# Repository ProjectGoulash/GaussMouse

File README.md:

# GaussMouse
The Project Goulash version of a DIY spacemouse

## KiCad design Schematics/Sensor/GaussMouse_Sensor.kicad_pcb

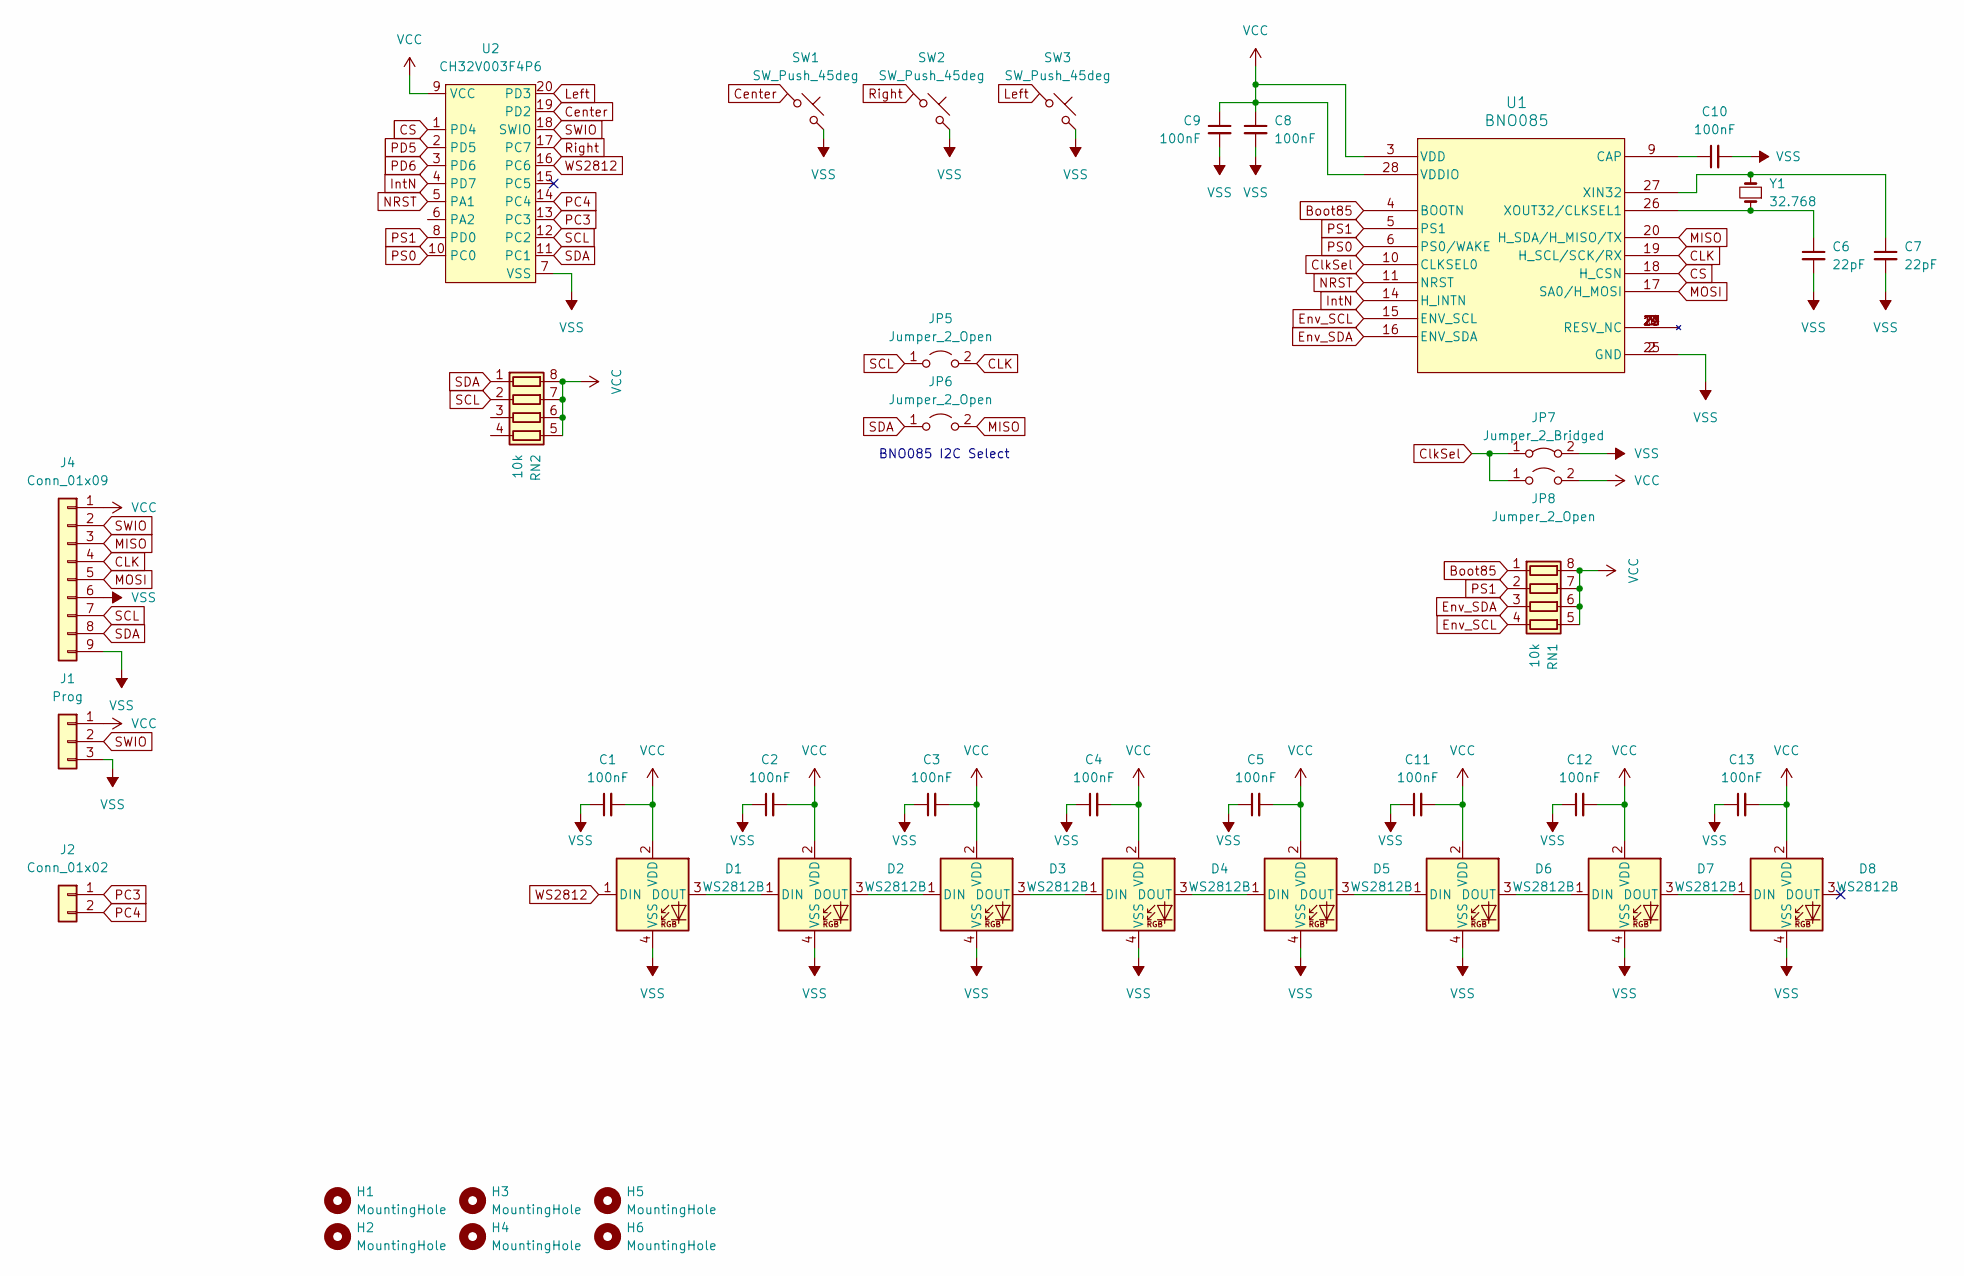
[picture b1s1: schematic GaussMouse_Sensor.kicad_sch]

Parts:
C1, C2, C3, C4, C5, C8, C9, C10, C11, C12, C13: 100nF; C_0805_2012Metric
C6, C7: 22pF; C_0805_2012Metric
D1, D2, D3, D4, D5, D6, D7, D8: WS2812B; SK6812SIDE-A-RVS
H1, H2, H3, H4, H5, H6: MountingHole; MountingHole_2.2mm_M2
J1: Prog; PinHeader_1x03_P2.54mm_Vertical
J2: Conn_01x02; PinHeader_1x02_P2.54mm_Vertical
J4: Conn_01x09; CON_526100933_MOL
JP5, JP6, JP8: Jumper_2_Open; SolderJumper-2_P1.3mm_Open_TrianglePad1.0x1.5mm
JP7: Jumper_2_Bridged; SolderJumper-2_P1.3mm_Bridged_Pad1.0x1.5mm
RN1, RN2: 10k; R_Array_Convex_4x0603
SW1, SW2, SW3: SW_Push_45deg; SW_SPST_TL3342
U1: BNO085; LGA-28_5.2x3.8mm_P0.5mm
U2: CH32V003F4P6; TSSOP-20_4.4x6.5mm_P0.65mm
Y1: 32.768; Crystal_SMD_3215-2Pin_3.2x1.5mm

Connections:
Boot85: RN1.1 (R1.1), U1.4 (BOOTN)
CLK: J4.4, JP5.2 (B), U1.19 (H_SCL/SCK/RX)
CS: U1.18 (H_CSN), U2.1 (PD4)
Center: SW1.1, U2.19 (PD2)
ClkSel: JP7.1 (A), JP8.1 (A), U1.10 (CLKSEL0)
Env_SCL: RN1.4 (R4.1), U1.15 (ENV_SCL)
Env_SDA: RN1.3 (R3.1), U1.16 (ENV_SDA)
IntN: U1.14 (H_INTN), U2.4 (PD7)
Left: SW3.1, U2.20 (PD3)
MISO: J4.3, JP6.2 (B), U1.20 (H_SDA/H_MISO/TX)
MOSI: J4.5, U1.17 (SA0/H_MOSI)
NRST: U1.11 (NRST), U2.5 (PA1)
unnamed: D1.3 (DOUT), D2.1 (DIN)
unnamed: D2.3 (DOUT), D3.1 (DIN)
unnamed: D3.3 (DOUT), D4.1 (DIN)
unnamed: D4.3 (DOUT), D5.1 (DIN)
unnamed: D5.3 (DOUT), D6.1 (DIN)
unnamed: D6.3 (DOUT), D7.1 (DIN)
unnamed: D7.3 (DOUT), D8.1 (DIN)
unnamed: C10.1, U1.9 (CAP)
unnamed: C7.1, U1.27 (XIN32), Y1.2
unnamed: C6.1, U1.26 (XOUT32/CLKSEL1), Y1.1
PC3: J2.1, U2.13 (PC3)
PC4: J2.2, U2.14 (PC4)
PD5: U2.2 (PD5)
PD6: U2.3 (PD6)
PS0: U1.6 (PS0/WAKE), U2.10 (PC0)
PS1: RN1.2 (R2.1), U1.5 (PS1), U2.8 (PD0)
Right: SW2.1, U2.17 (PC7)
SCL: J4.7, JP5.1 (A), RN2.2 (R2.1), U2.12 (PC2)
SDA: J4.8, JP6.1 (A), RN2.1 (R1.1), U2.11 (PC1)
SWIO: J1.2, J4.2, U2.18 (SWIO)
VCC: C1.2, C2.2, C3.2, C4.2, C5.2, C8.1, C9.1, C11.2, C12.2, C13.2, D1.2 (VDD), D2.2 (VDD), D3.2 (VDD), D4.2 (VDD), D5.2 (VDD), D6.2 (VDD), D7.2 (VDD), D8.2 (VDD), J1.1, J4.1, JP8.2 (B), RN1.5 (R4.2), RN1.6 (R3.2), RN1.7 (R2.2), RN1.8 (R1.2), RN2.5 (R4.2), RN2.6 (R3.2), RN2.7 (R2.2), RN2.8 (R1.2), U1.3 (VDD), U1.28 (VDDIO), U2.9 (VCC)
VSS: C1.1, C2.1, C3.1, C4.1, C5.1, C6.2, C7.2, C8.2, C9.2, C10.2, C11.1, C12.1, C13.1, D1.4 (VSS), D2.4 (VSS), D3.4 (VSS), D4.4 (VSS), D5.4 (VSS), D6.4 (VSS), D7.4 (VSS), D8.4 (VSS), J1.3, J4.6, J4.9, JP7.2 (B), SW1.2, SW2.2, SW3.2, U1.2 (GND), U1.25 (GND), U2.7 (VSS)
WS2812: D1.1 (DIN), U2.16 (PC6)

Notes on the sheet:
BNO085 I2C Select

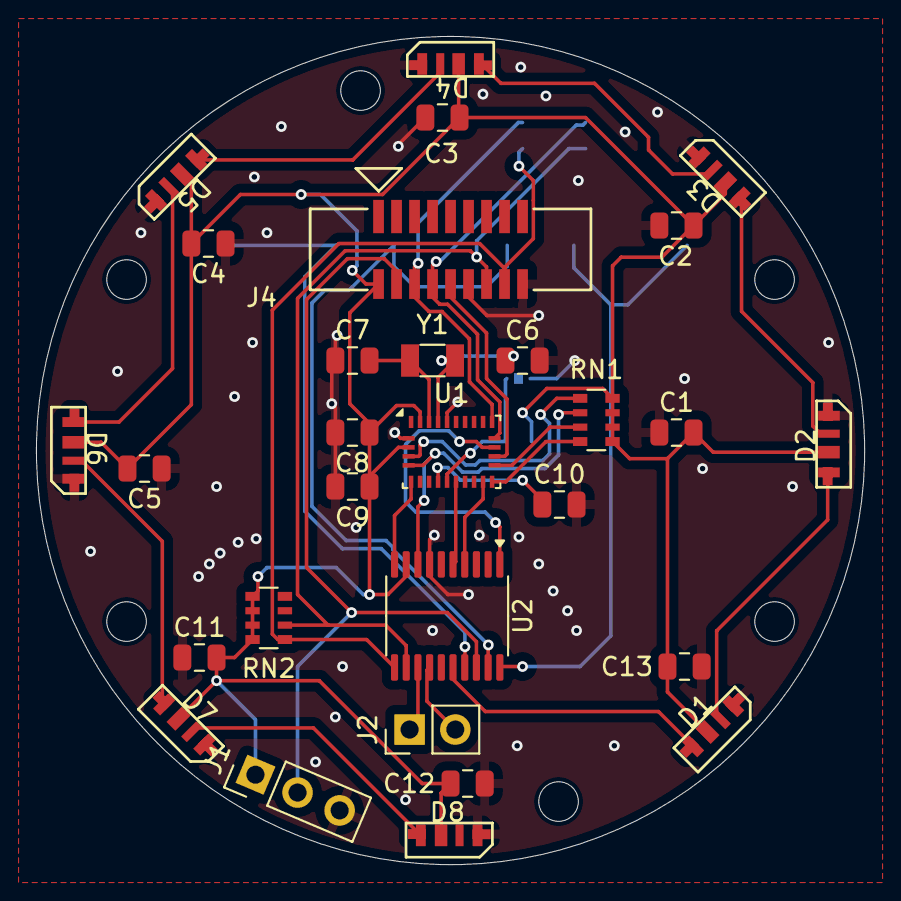
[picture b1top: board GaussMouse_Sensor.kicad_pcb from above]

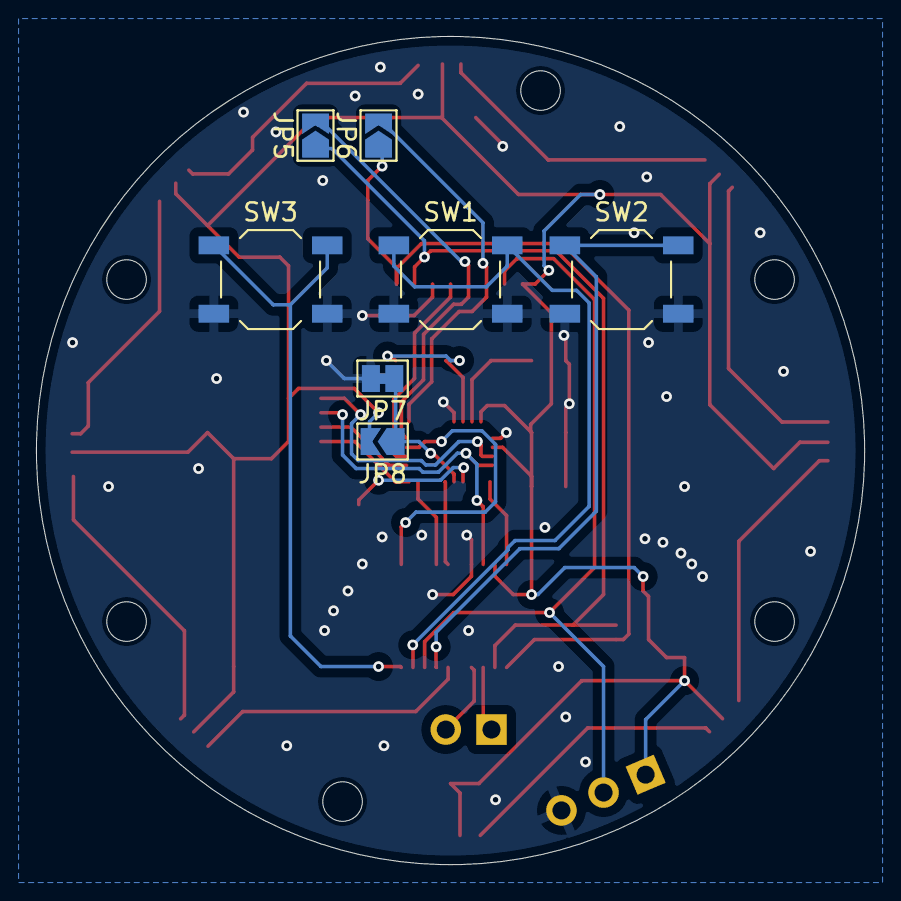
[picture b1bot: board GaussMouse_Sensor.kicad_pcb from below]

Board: 2 copper layers, 46.0 x 46.0 mm, 42 parts (7 on the bottom side), 33 nets.

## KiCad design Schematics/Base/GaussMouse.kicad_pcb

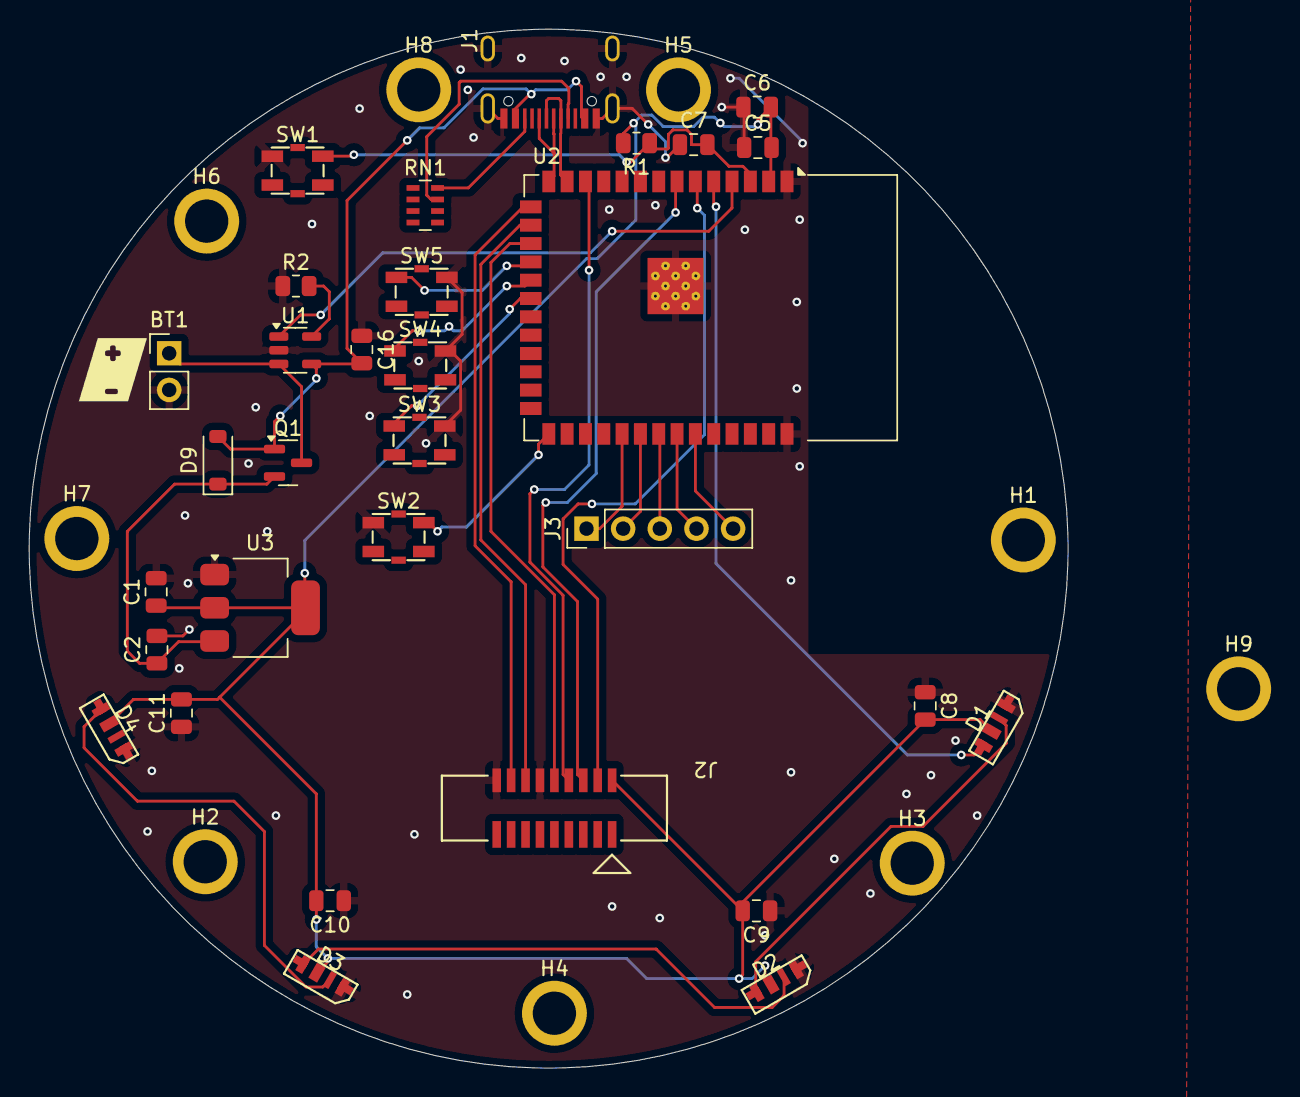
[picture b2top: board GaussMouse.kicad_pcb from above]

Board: 2 copper layers, 72.0 x 72.0 mm, 41 parts (0 on the bottom side), 31 nets.

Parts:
BT1: Battery_Cell; PinHeader_1x02_P2.54mm_Vertical
C1, C2: 10uF; C_0805_2012Metric
C5, C7, C8, C9, C10, C11: 100nF; C_0805_2012Metric
C6, C16: 22uF; C_0805_2012Metric
D1, D2, D3, D4: WS2812B; SK6812SIDE-A-RVS
D9: D_Schottky; D_SOD-123
H1, H2, H3, H4, H5, H6, H7, H8, H9: MountingHole; M2ThreadedStandoff
J1: USB_C_Receptacle; USB_C_Receptical-Jing
J2: Conn_01x09; CON_526100933_MOL
J3: Conn_01x05; PinHeader_1x05_P2.54mm_Vertical
Q1: AO3401A; SOT-23
R1, R2: R_Small; R_0805_2012Metric
RN1: 5.1k; R_Array_Concave_4x0603
SW1, SW2: SW_SPST; TS3315A
SW3, SW4, SW5: SW_Push_45deg; TS3315A
U1: LTC4054ES5; TSOT-23-5
U2: ESP32-S3-WROOM-1
U3: TLV1117-33; SOT-223-3_TabPin2
kibuzzard-665A311B: G***; kibuzzard-665A311B

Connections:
+5V: C16.2, D9.2 (A), J1.A4 (VBUS), J1.A9 (VBUS), J1.B4 (VBUS), J1.B9 (VBUS), Q1.1 (G), U1.4 (V_{CC})
/D+: J1.A6 (D+), J1.B6 (D+), U2.14 (IO20)
/D-: J1.A7 (D-), J1.B7 (D-), U2.13 (IO19)
CLK: J2.4, U2.12 (IO8)
Center: SW3.1, U2.20 (IO12)
Charge_Status: U1.1 (~CHRG), U2.4 (IO4)
Left: SW5.1, U2.18 (IO10)
MISO: J2.3, U2.7 (IO7)
MOSI: J2.5, U2.17 (IO9)
unnamed: BT1.1 (+), Q1.3 (D), U1.3 (BAT)
unnamed: D1.3 (DOUT), D2.1 (DIN)
unnamed: D2.3 (DOUT), D3.1 (DIN)
unnamed: D3.3 (DOUT), D4.1 (DIN)
unnamed: C2.1, D9.1 (K), Q1.2 (S), U3.3 (VI)
unnamed: J1.A5 (CC1), RN1.7 (R2.2)
unnamed: J1.B5 (CC2), RN1.8 (R1.2)
unnamed: J3.1, U2.31 (IO38)
unnamed: J3.2, U2.32 (IO39)
unnamed: J3.3, U2.33 (IO40)
unnamed: J3.4, U2.34 (IO41)
unnamed: J3.5, U2.35 (IO42)
unnamed: C7.2, R1.1, SW1.2 (B), U2.3 (EN)
unnamed: SW2.2 (B), U2.27 (IO0)
unnamed: R2.2, U1.5 (PROG)
Right: SW4.1, U2.19 (IO11)
SCL: J2.7, U2.16 (IO46)
SDA: J2.8, U2.15 (IO3)
SWIO: J2.2, U2.6 (IO6)
VCC: C1.1, C5.2, C6.2, C8.2, C9.2, C10.2, C11.2, D1.2 (VDD), D2.2 (VDD), D3.2 (VDD), D4.2 (VDD), J2.1, R1.2, U2.2 (3V3), U3.2 (VO)
VSS: BT1.2 (-), C1.2, C2.2, C5.1, C6.1, C7.1, C8.1, C9.1, C10.1, C11.1, C16.1, D1.4 (VSS), D2.4 (VSS), D3.4 (VSS), D4.4 (VSS), J1.A1 (GND), J1.A12 (GND), J1.B1 (GND), J1.B12 (GND), J1.S1 (SHIELD), J2.6, J2.9, R2.1, SW1.1 (A), SW2.1 (A), SW3.2, SW4.2, SW5.2, U1.2 (GND), U2.1 (GND), U2.40 (GND), U2.41 (GND), U3.1 (GND)
WS2812: D1.1 (DIN), U2.5 (IO5)

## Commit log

2024-05-08 Started
2024-05-09 Further Progress
2024-05-10 Sensor Board Ready for Traces
2025-01-28 Commit for backup. Short on sensor board so I'm going to redo it
